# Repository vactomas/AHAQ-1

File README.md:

# AHAQ-1 -> AstroHex Air Quality v1

AHAQ-1 is an air quality station. Currently, it is an on-going project in development.

This device is based on the ESP32-C6 microcontroller. It features SCD4X CO2 sensor, BMP280 for temperature and ambient pressure measurements and SEN55 for PM1-10, NOx and VOCs. Additionaly, there are two I2C expansion ports for additional sensors. There is also a connector for E-Paper display.

ESPhome is the firmware of choice for AHAQ-1. This allows for easy integration with Home Assistant instances.

This repo contains all the necessary files to build and flash this device.

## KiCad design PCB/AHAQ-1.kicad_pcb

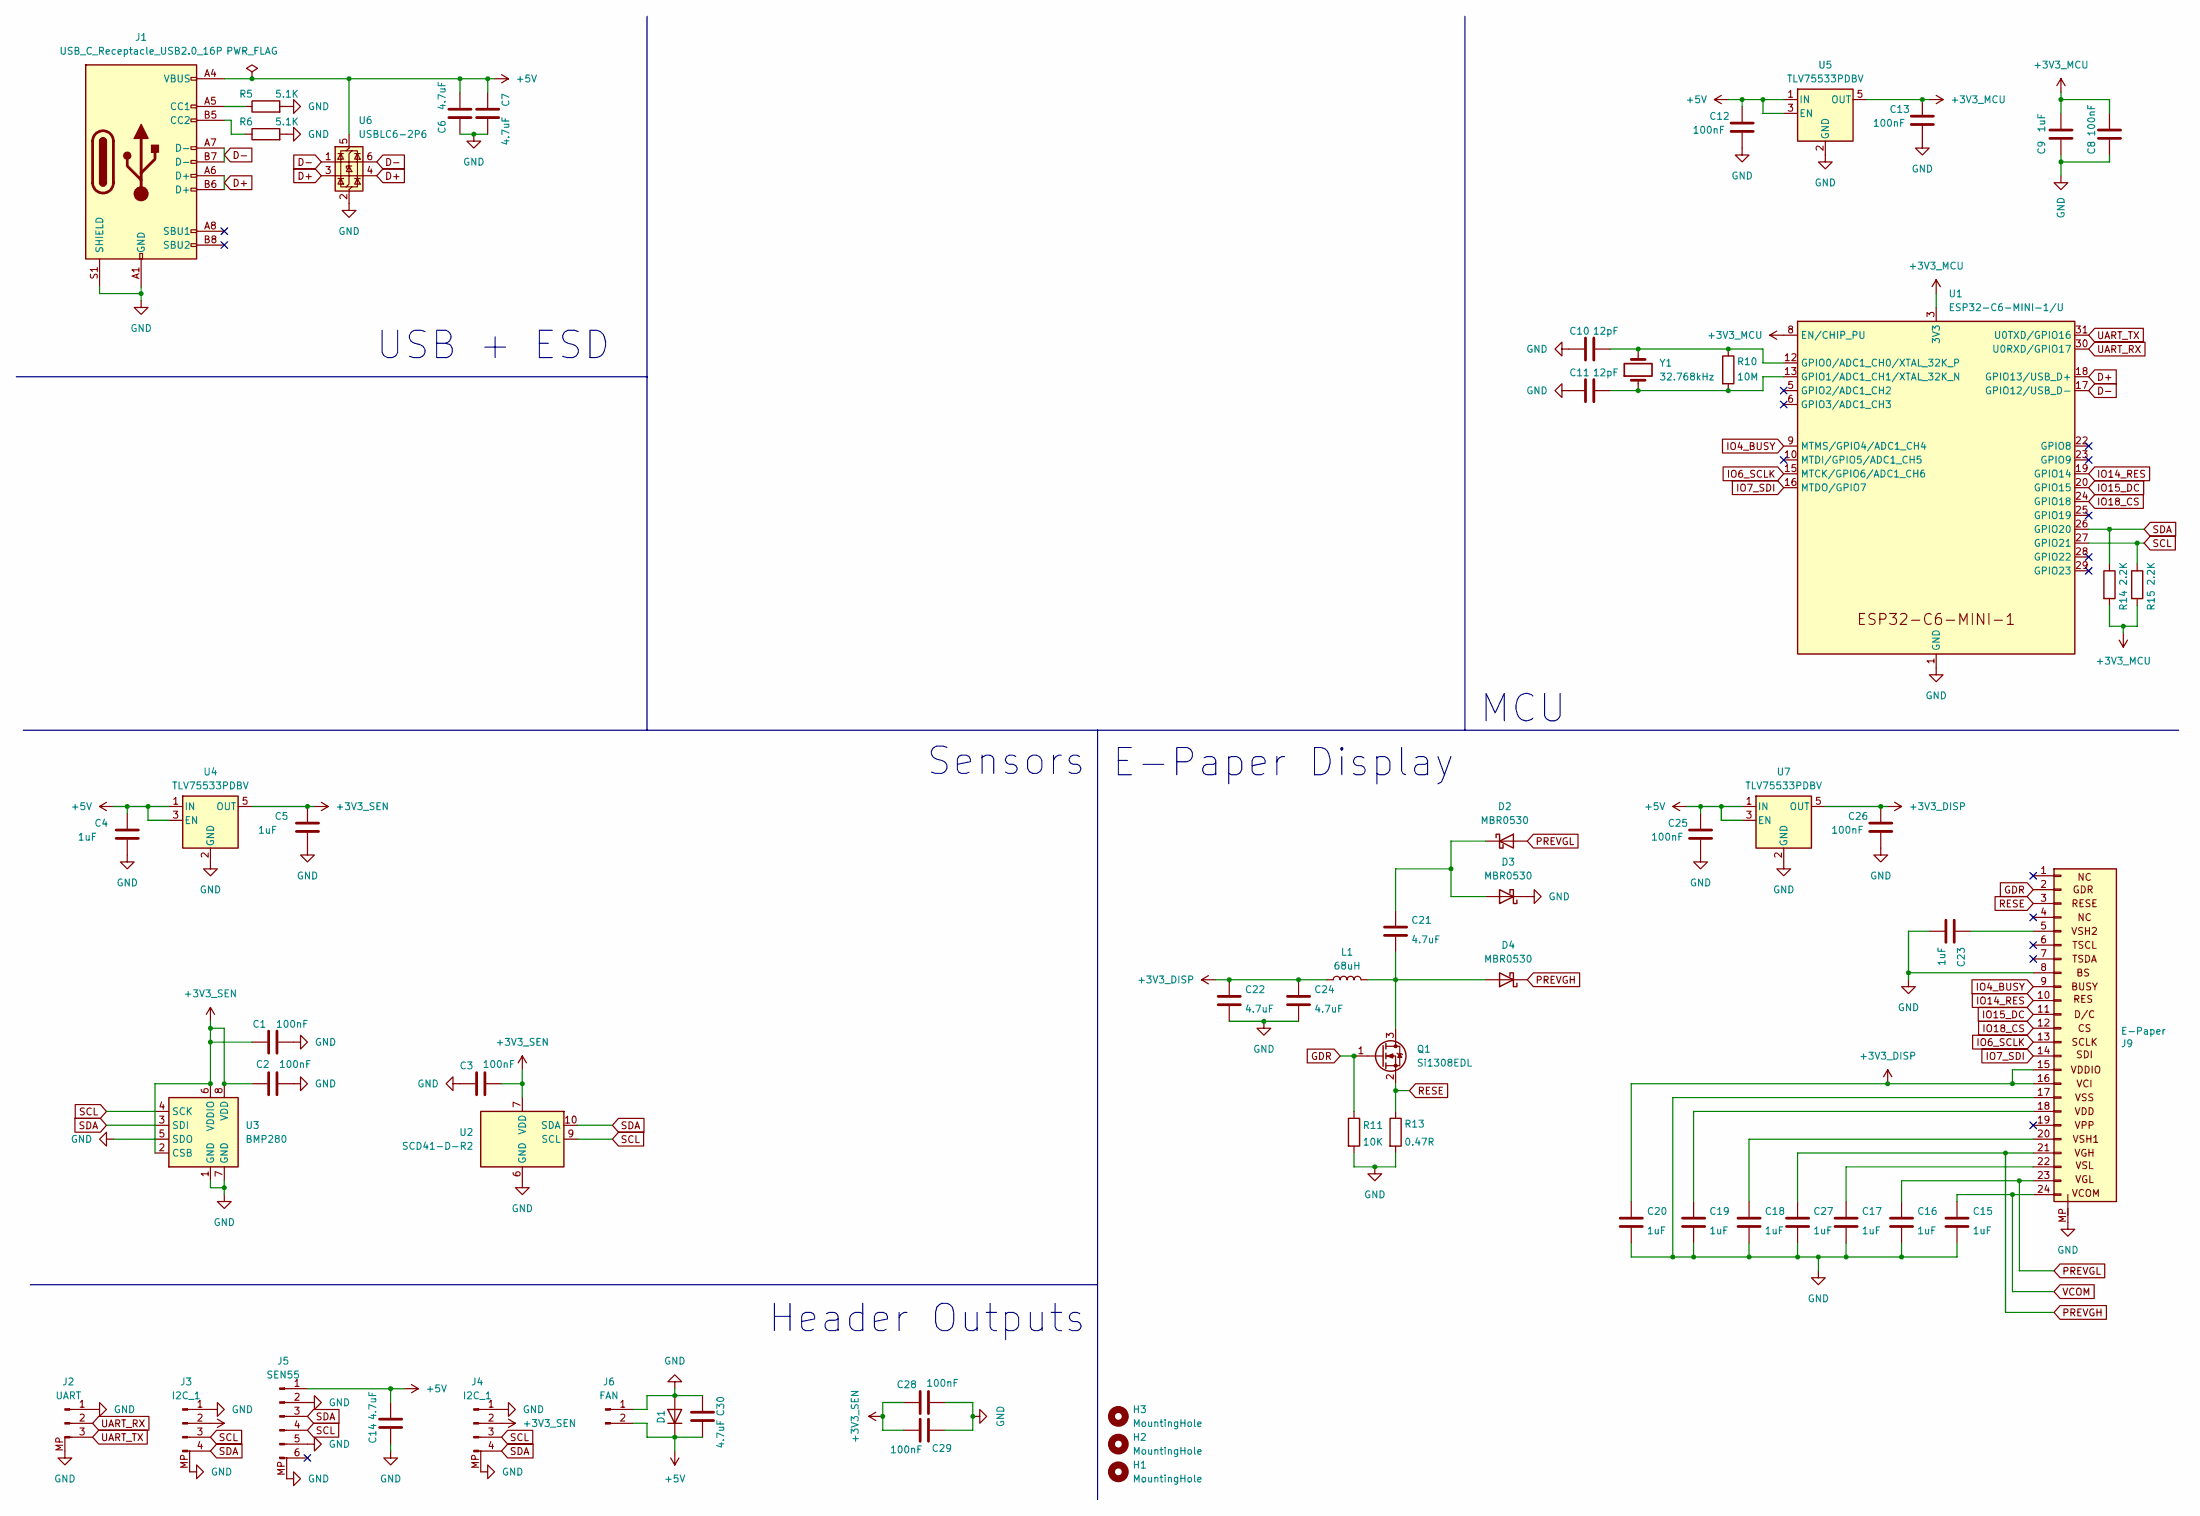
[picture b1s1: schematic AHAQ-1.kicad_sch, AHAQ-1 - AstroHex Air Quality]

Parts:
C1, C2, C3, C8, C12, C13, C25, C26, C28, C29: 100nF; C_0603_1608Metric
C4, C5, C9, C15, C16, C17, C18, C19, C20, C23, C27: 1uF; C_0603_1608Metric
C6, C7, C14, C21, C22, C24, C30: 4.7uF; C_0805_2012Metric
C10, C11: 12pF; C_0805_2012Metric
D1: D; D_0603_1608Metric
D2, D3, D4: MBR0530; D_SOD-123
H1, H2, H3: MountingHole; MountingHole_2.2mm_M2_ISO7380
J1: USB_C_Receptacle_USB2.0_16P; USB_C_Receptacle_GCT_USB4105-xx-A_16P_TopMnt_Horizontal
J2: UART; JST_SH_SM03B-SRSS-TB_1x03-1MP_P1.00mm_Horizontal
J3, J4: I2C_1; JST_SH_SM04B-SRSS-TB_1x04-1MP_P1.00mm_Horizontal
J5: SEN55; JST_GH_BM06B-GHS-TBT_1x06-1MP_P1.25mm_Vertical
J6: FAN; JST_PH_B2B-PH-K_1x02_P2.00mm_Vertical
J9: E-Paper; Hirose_FH12-24S-0.5SH_1x24-1MP_P0.50mm_Horizontal
L1: 68uH; L_0805_2012Metric
Q1: Si1308EDL; SOT-323_SC-70
R5, R6: 5.1K; R_0603_1608Metric
R10: 10M; R_0402_1005Metric
R11: 10K; R_0603_1608Metric
R13: 0.47R; R_0805_2012Metric
R14, R15: 2.2K; R_0603_1608Metric
U1: ESP32-C6-MINI-1/U; ESP32-C6-MINI-1
U2: SCD41-D-R2; Sensirion_SCD4x-1EP_10.1x10.1mm_P1.25mm_EP4.8x4.8mm
U3: BMP280; Bosch_LGA-8_2x2.5mm_P0.65mm_ClockwisePinNumbering
U4, U5, U7: TLV75533PDBV; SOT-23-5
U6: USBLC6-2P6; SOT-666
Y1: 32.768kHz; Crystal_SMD_3215-2Pin_3.2x1.5mm

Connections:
+3V3_DISP: C20.1, C22.1, C24.1, C26.1, J9.15, J9.16, L1.1, U7.5 (OUT)
+3V3_SEN: C1.2, C2.1, C3.1, C5.1, C28.2, C29.1, J3.2, J4.2, U2.7 (VDD), U2.19 (VDD), U3.2 (CSB), U3.6 (VDDIO), U3.8 (VDD), U4.5 (OUT)
D+: J1.A6 (D+), J1.B6 (D+), U1.18 (GPIO13/USB_D+), U6.3 (I/O2), U6.4 (I/O2)
D-: J1.A7 (D-), J1.B7 (D-), U1.17 (GPIO12/USB_D-), U6.1 (I/O1), U6.6 (I/O1)
GDR: J9.2, Q1.1 (G), R11.1
GND: C1.1, C2.2, C3.2, C4.2, C5.2, C6.2, C7.1, C8.2, C9.2, C10.2, C11.2, C12.2, C13.2, C14.2, C15.2, C16.2, C17.2, C18.2, C19.2, C20.2, C22.2, C23.2, C24.2, C25.2, C26.2, C27.2, C28.1, C29.2, C30.2, D1.2 (A), D3.1 (K), J1.A1 (GND), J1.A12 (GND), J1.B1 (GND), J1.B12 (GND), J1.S1 (SHIELD), J2.1, J2.MP, J3.1, J3.MP, J4.1, J4.MP, J5.2, J5.5, J5.MP, J6.1, J9.8, J9.17, J9.MP, R5.2, R6.2, R11.2, R13.2, U1.1 (GND), U1.2 (GND), U1.11 (GND), U1.14 (GND), U1.36 (GND), U1.37 (GND), U1.38 (GND), U1.39 (GND), U1.40 (GND), U1.41 (GND), U1.42 (GND), U1.43 (GND), U1.44 (GND), U1.45 (GND), U1.46 (GND), U1.47 (GND), U1.48 (GND), U1.49 (GND), U1.50 (GND), U1.51 (GND), U1.52 (GND), U1.53 (GND), U2.6 (GND), U2.20 (GND), U2.21 (GND), U3.1 (GND), U3.5 (SDO), U3.7 (GND), U4.2 (GND), U5.2 (GND), U6.2 (GND), U7.2 (GND)
IO4_BUSY: J9.9, U1.9 (MTMS/GPIO4/ADC1_CH4)
IO6_SCLK: J9.13, U1.15 (MTCK/GPIO6/ADC1_CH6)
IO7_SDI: J9.14, U1.16 (MTDO/GPIO7)
IO14_RES: J9.10, U1.19 (GPIO14)
IO15_DC: J9.11, U1.20 (GPIO15)
IO18_CS: J9.12, U1.24 (GPIO18)
unnamed: C21.1, D2.1 (K), D3.2 (A)
unnamed: C21.2, D4.2 (A), L1.2, Q1.3 (D)
unnamed: J1.A5 (CC1), R5.1
unnamed: J1.B5 (CC2), R6.1
unnamed: C23.1, J9.5
unnamed: C19.1, J9.18
unnamed: C18.1, J9.20
unnamed: C17.1, J9.22
unnamed: C10.1, R10.1, U1.12 (GPIO0/ADC1_CH0/XTAL_32K_P), Y1.2
unnamed: C11.1, R10.2, U1.13 (GPIO1/ADC1_CH1/XTAL_32K_N), Y1.1
PREVGH: C27.1, D4.1 (K), J9.21
PREVGL: C16.1, D2.2 (A), J9.23
RESE: J9.3, Q1.2 (S), R13.1
SCL: J3.3, J4.3, J5.4, R15.1, U1.27 (GPIO21), U2.9 (SCL), U3.4 (SCK)
SDA: J3.4, J4.4, J5.3, R14.1, U1.26 (GPIO20), U2.10 (SDA), U3.3 (SDI)
UART_RX: J2.2, U1.30 (U0RXD/GPIO17)
UART_TX: J2.3, U1.31 (U0TXD/GPIO16)
VCOM: C15.1, J9.24

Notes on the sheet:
Header Outputs
USB + ESD
E-Paper Display
Sensors
MCU

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
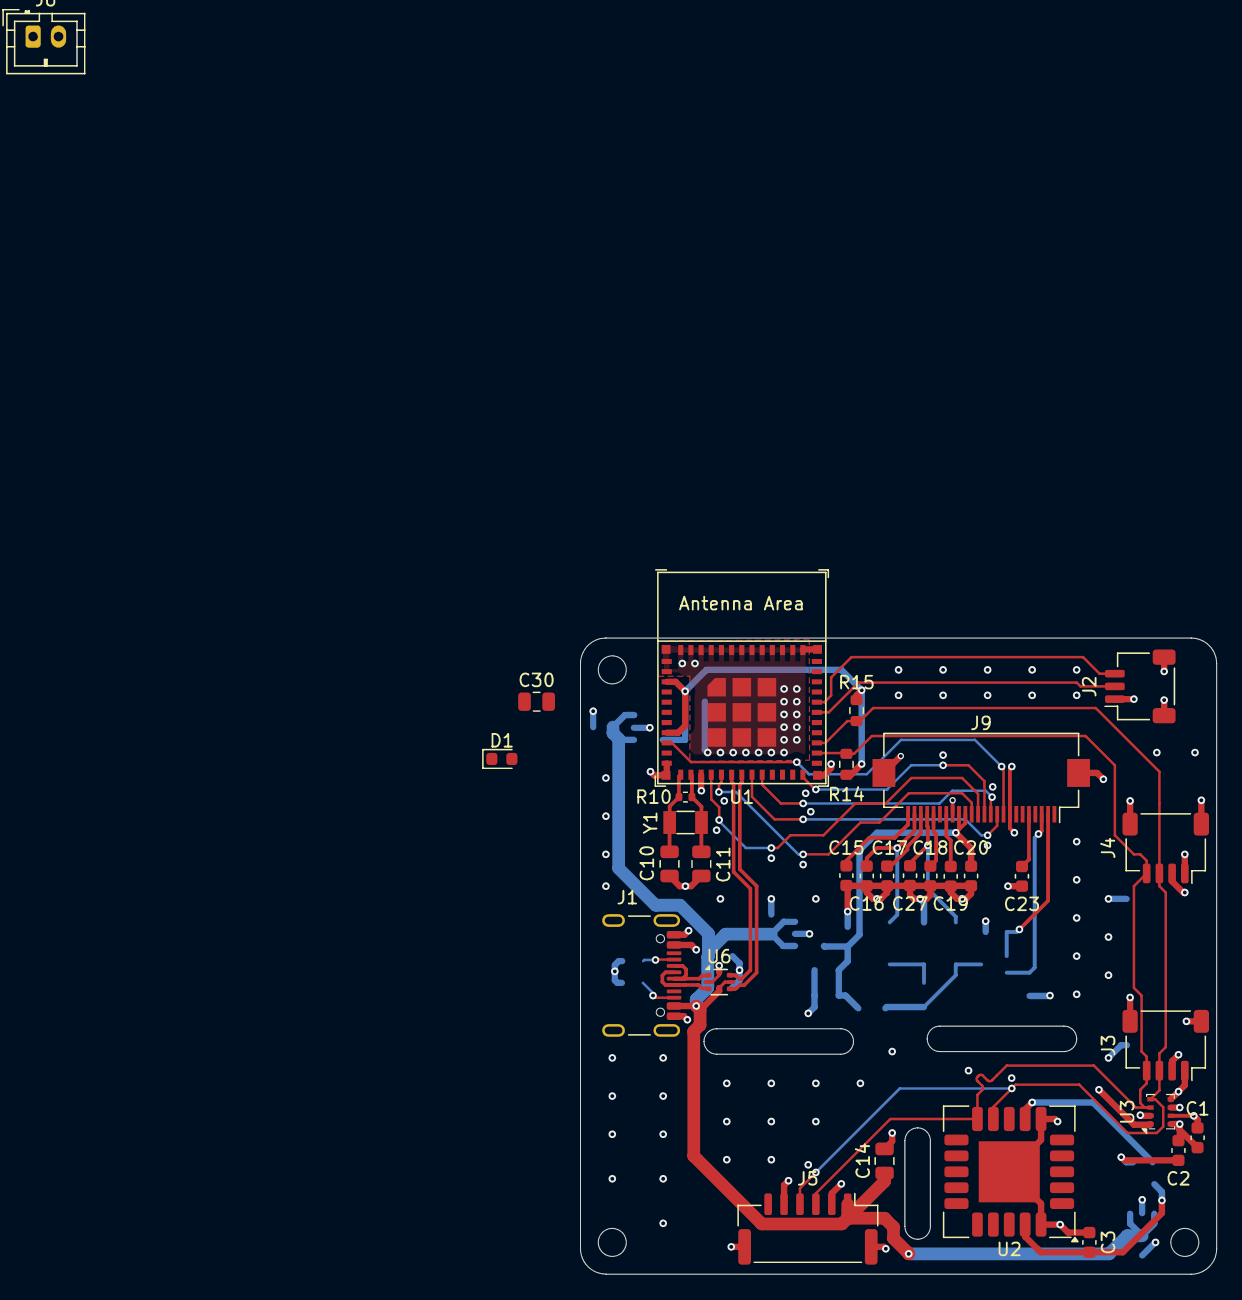
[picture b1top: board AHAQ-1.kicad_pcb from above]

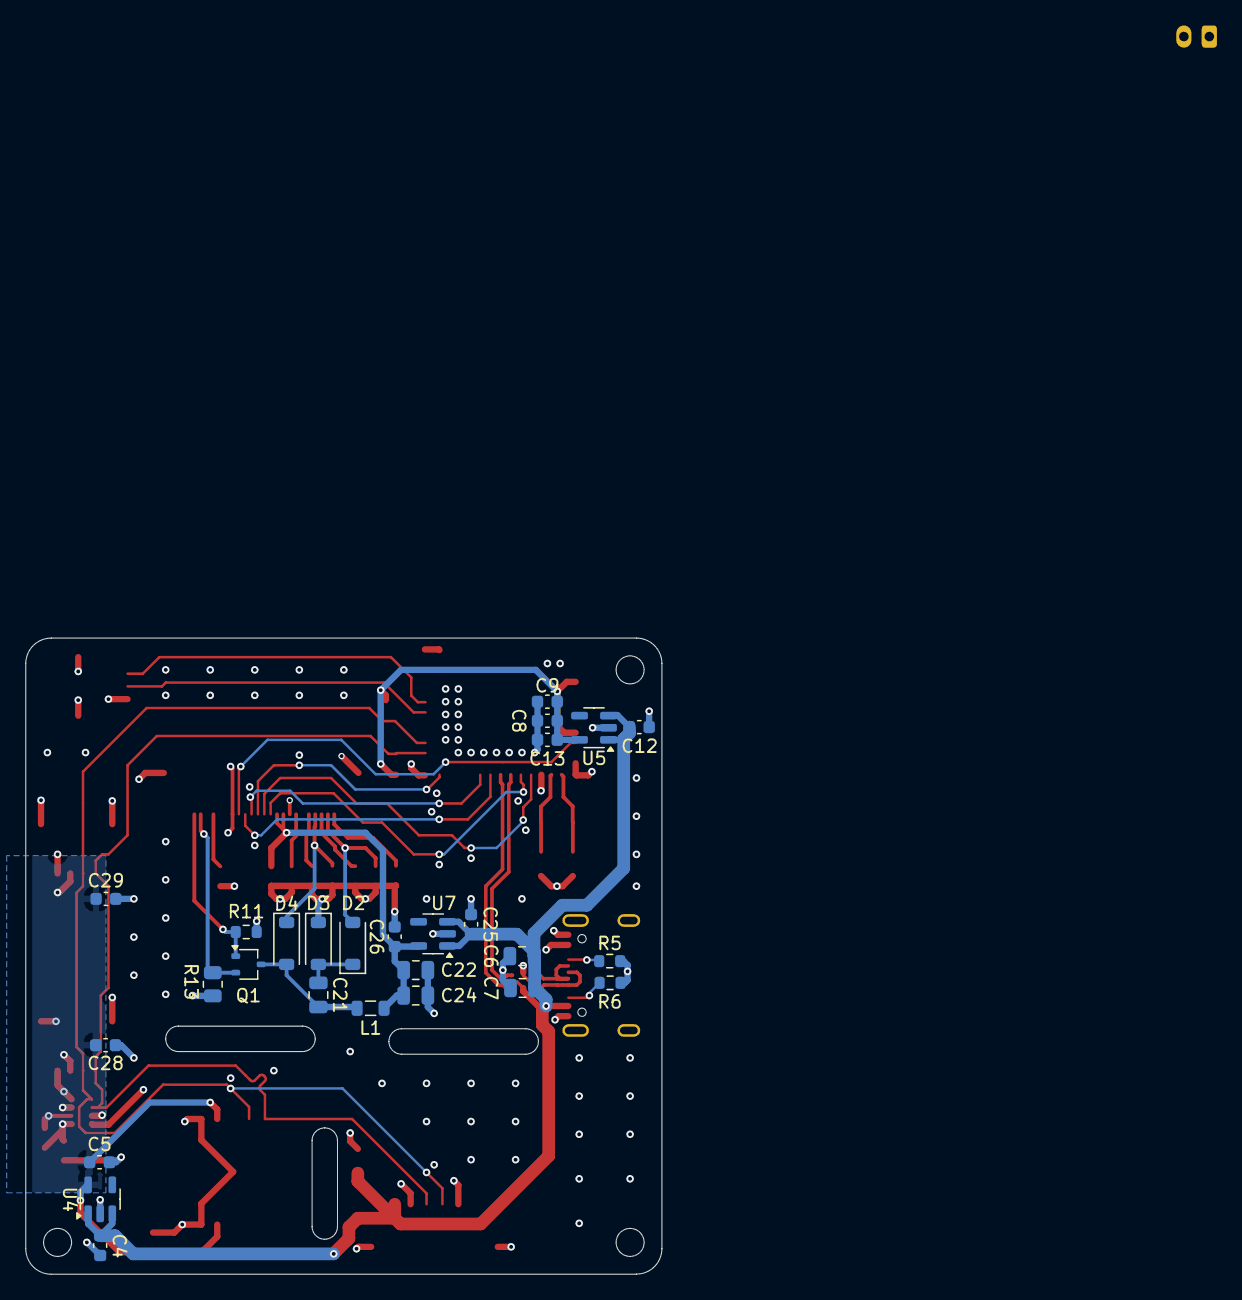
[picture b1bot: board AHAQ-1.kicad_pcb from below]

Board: 4 copper layers, 50.0 x 50.0 mm, 61 parts (27 on the bottom side), 32 nets.

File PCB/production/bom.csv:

Designator,Footprint,Quantity,Value,LCSC Part #
"C1, C12, C13, C2, C25, C26, C28, C29, C3, C30, C8",0603,11,100nF,
"C10, C11",0805,2,12pF,
"C14, C21, C22, C24, C6, C7",0805,6,4.7uF,
"C15, C16, C17, C18, C19, C20, C23, C27, C4, C5, C9",0603,11,1uF,
"D2, D3, D4",D_SOD-123,3,MBR0530,
J1,USB_C_Receptacle_GCT_USB4105-xx-A_16P_TopMnt_Horizontal,1,USB_C_Receptacle_USB2.0_16P,
J2,JST_SH_BM03B-SRSS-TB_1x03-1MP_P1.00mm_Vertical,1,UART,
J3,JST_SH_BM04B-SRSS-TB_1x04-1MP_P1.00mm_Vertical,1,I2C_3,
J4,JST_GH_BM06B-GHS-TBT_1x06-1MP_P1.25mm_Vertical,1,SEN55,
J5,JST_SH_BM04B-SRSS-TB_1x04-1MP_P1.00mm_Vertical,1,I2C_1,
J6,JST_SH_BM04B-SRSS-TB_1x04-1MP_P1.00mm_Vertical,1,I2C_2,
J9,Hirose_FH12-24S-0.5SH_1x24-1MP_P0.50mm_Horizontal,1,E-Paper,
L1,0805,1,68uH,
Q1,SOT-323_SC-70,1,Si1308EDL,
R10,0402,1,10M,
R11,0603,1,10K,
R13,0805,1,0.47R,
"R14, R15",0603,2,2.2K,
"R5, R6",0603,2,5.1K,
U1,ESP32-C6-MINI-1,1,ESP32-C6-MINI-1/U,
U2,Sensirion_SCD4x-1EP_10.1x10.1mm_P1.25mm_EP4.8x4.8mm,1,SCD41-D-R2,
U3,Bosch_LGA-8_2x2.5mm_P0.65mm_ClockwisePinNumbering,1,BMP280,
"U4, U5, U7",SOT-23-5,3,TLV75533PDBV,
U6,SOT-666,1,USBLC6-2P6,
Y1,Crystal_SMD_3215-2Pin_3.2x1.5mm,1,32.768kHz,

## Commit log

2024-12-15 Update issue templates
2024-12-16 Add ESD component
2024-12-17 Add E-Paper and Headers to schematic
2024-12-17 ERC check and fixes
2024-12-18 First PCB layout, added mounting holes and PCB footprint
2024-12-26 Updated schematic, finished PCB layout and routing
2024-12-26 Update PDF schematic
2024-12-27 Drop battery support, add stitching vias and decooupling capacitors
2024-12-28 Improved LDOs, dropped one extension port
2024-12-28 Rename to AHQA-1, README
2025-01-04 Added FAN output
